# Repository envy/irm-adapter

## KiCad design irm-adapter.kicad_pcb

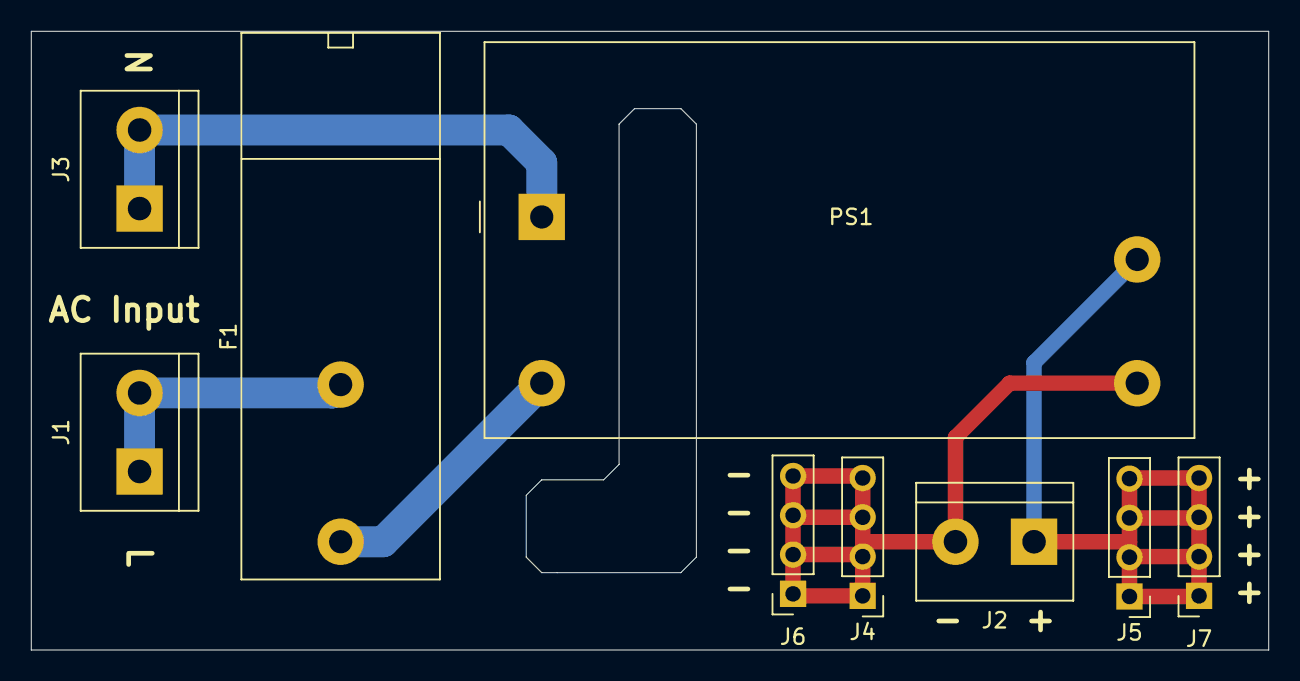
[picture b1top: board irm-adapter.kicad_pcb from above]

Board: 2 copper layers, 80.0 x 40.0 mm, 9 parts (0 on the bottom side), 5 nets.

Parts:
F1: Fuse; Fuseholder_Cylinder-5x20mm_Bulgin_FX0457_Horizontal_Closed
J1: L; TerminalBlock_bornier-2_P5.08mm
J2: Vout; TerminalBlock_bornier-2_P5.08mm
J3: N; TerminalBlock_bornier-2_P5.08mm
J4, J5: 1x4; PinHeader_1x04_P2.54mm_Vertical
J6, J7: 1x4; PinSocket_1x04_P2.54mm_Vertical
PS1: IRM-05-5; Converter_ACDC_MeanWell_IRM-05-xx_THT

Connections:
/+5V: J2.1, J5.1, J5.2, J5.3, J5.4, J7.1, J7.2, J7.3, J7.4, PS1.4
/GND: J2.2, J4.1, J4.2, J4.3, J4.4, J6.1, J6.2, J6.3, J6.4, PS1.3
/L: F1.2, J1.1, J1.2
/L_F: F1.1, PS1.2
/N: J3.1, J3.2, PS1.1

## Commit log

2019-03-31 first version
2019-03-31 reichelt urls
2019-04-01 added headers for Vout
2019-04-01 some changes
